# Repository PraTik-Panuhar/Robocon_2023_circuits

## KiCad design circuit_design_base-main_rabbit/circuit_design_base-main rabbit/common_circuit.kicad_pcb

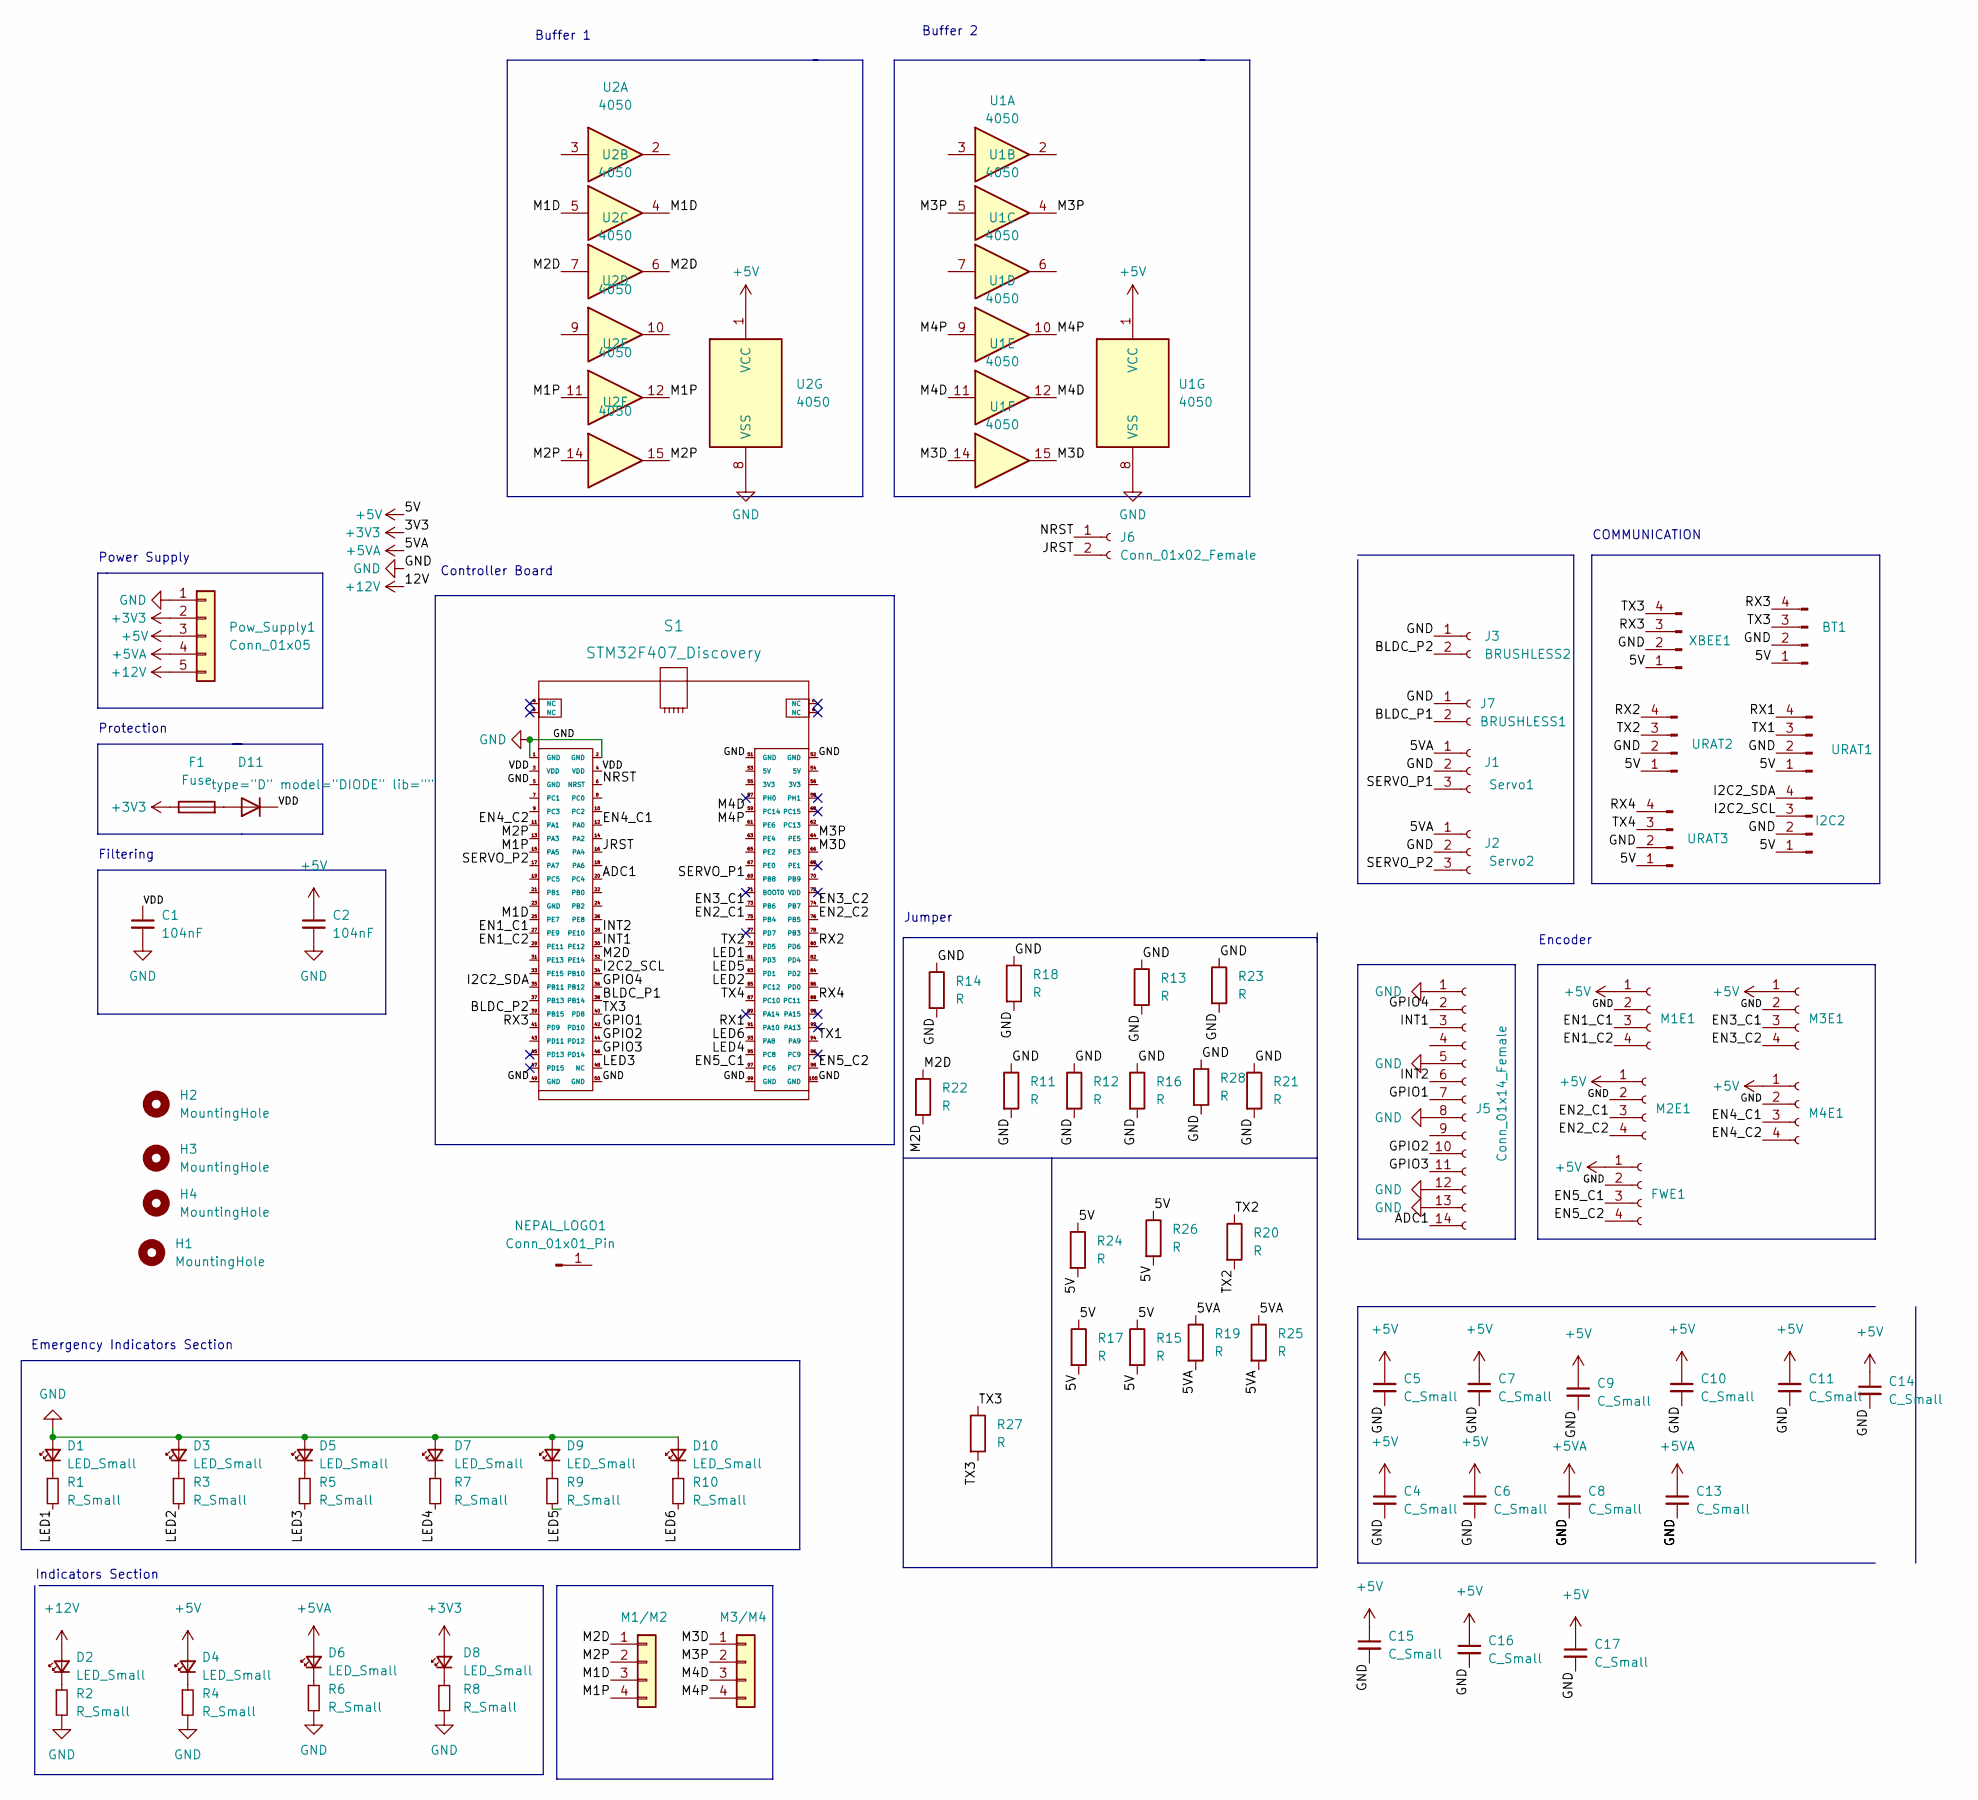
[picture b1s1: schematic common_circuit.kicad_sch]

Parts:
BT1: Conn_01x04_Male; jst_4
C1, C2: 104nF; Capacitor_Disc_Small
C4, C5, C6, C7, C8, C9, C10, C11, C13, C14, C15, C16, C17: C_Small; Capacitor_Disc_Small
D1, D2, D3, D4, D5, D6, D7, D8, D9, D10: LED_Small; LED_D3.0mm
D11: type="D" model="DIODE" lib=""; Diode_Medium
F1: Fuse; Fuse_Holder
FWE1: Conn_01x04_Female; jst_4
H1, H2, H3, H4: MountingHole; MountingHole_3mm_Pad
I2C2: I2C1; jst_4
J1: Servo1; JST_EH_B3B-EH-A_1x03_P2.50mm_Vertical
J2: Servo2; JST_EH_B3B-EH-A_1x03_P2.50mm_Vertical
J3: BRUSHLESS2; PinHeader_1x02_P2.54mm_Vertical
J5: Conn_01x14_Female; IDC-Header_2x07_P2.54mm_Latch_Vertical
J6: Conn_01x02_Female; PinHeader_1x02_P2.54mm_Vertical
J7: BRUSHLESS1; PinHeader_1x02_P2.54mm_Vertical
M1/M2, M3/M4: Conn_01x04; jst_4
M1E1, M2E1, M3E1, M4E1: Conn_01x04_Female; jst_4
NEPAL_LOGO1: Conn_01x01_Pin; nepalLogo
Pow_Supply1: Conn_01x05; JST_5_BIG
R1, R2, R3, R4, R5, R6, R7, R8, R9, R10: R_Small; Resistor_small
R11, R12, R13, R14, R15, R16, R17, R18, R19, R21, R22, R23, R25, R26, R28: R; Resistor_small
R20, R24, R27: R; R_Axial_DIN0207_L6.3mm_D2.5mm_P15.24mm_Horizontal
S1: STM32F407_Discovery
U1, U2: 4050; DIP-16_W7.62mm_LongPads
URAT1, URAT2, URAT3: Conn_01x04_Male; jst_4
XBEE1: Conn_01x04_Male; jst_4

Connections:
+3V3: D8.2 (A), F1.1, Pow_Supply1.2
+5V: BT1.1, C2.1, C4.1, C5.1, C6.1, C7.1, C9.1, C10.1, C11.1, C14.1, C15.1, C16.1, C17.1, D4.2 (A), FWE1.1, I2C2.1, M1E1.1, M2E1.1, M3E1.1, M4E1.1, Pow_Supply1.3, R15.1, R15.2, R17.1, R17.2, R24.1, R24.2, R26.1, R26.2, U1.1 (VCC), U2.1 (VCC), URAT1.1, URAT2.1, URAT3.1, XBEE1.1
+5VA: C8.1, C13.1, D6.2 (A), J1.1, J2.1, Pow_Supply1.4, R19.1, R19.2, R25.1, R25.2
+12V: D2.2 (A), Pow_Supply1.5
/ADC1: J5.14, S1.20 (PC4)
/BLDC_P1: J7.2, S1.38 (PB14)
/BLDC_P2: J3.2, S1.39 (PB15)
/EN1_C1: M1E1.3, S1.27 (PE9)
/EN1_C2: M1E1.4, S1.29 (PE11)
/EN2_C1: M2E1.3, S1.75 (PB4)
/EN2_C2: M2E1.4, S1.76 (PB5)
/EN3_C1: M3E1.3, S1.73 (PB6)
/EN3_C2: M3E1.4, S1.74 (PB7)
/EN4_C1: M4E1.3, S1.12 (PA0)
/EN4_C2: M4E1.4, S1.11 (PA1)
/EN5_C1: FWE1.3, S1.97 (PC6)
/EN5_C2: FWE1.4, S1.98 (PC7)
/GPIO1: J5.7, S1.42 (PD10)
/GPIO2: J5.10, S1.44 (PD12)
/GPIO3: J5.11, S1.46 (PD14)
/GPIO4: J5.2, S1.36 (PB12)
/I2C2_SCL: I2C2.3, S1.34 (PB10)
/I2C2_SDA: I2C2.4, S1.35 (PB11)
/INT1: J5.3, S1.30 (PE12)
/INT2: J5.6, S1.28 (PE10)
/JRST: J6.2, S1.16 (PA4)
/LED1: R1.2, S1.81 (PD3)
/LED2: R3.2, S1.85 (PC12)
/LED3: R5.2, S1.48 (NC)
/LED4: R7.2, S1.95 (PC8)
/LED5: R9.2, S1.83 (PD1)
/LED6: R10.2, S1.93 (PA8)
/M1D: M1/M2.3, S1.25 (PE7), U2.4, U2.5
/M1P: M1/M2.4, S1.15 (PA5), U2.11, U2.12
/M2D: M1/M2.1, R22.1, R22.2, S1.32 (PE14), U2.6, U2.7
/M2P: M1/M2.2, S1.13 (PA3), U2.14, U2.15
/M3D: M3/M4.1, S1.66 (PE3), U1.14, U1.15
/M3P: M3/M4.2, S1.64 (PE5), U1.4, U1.5
/M4D: M3/M4.3, S1.59 (PC14), U1.11, U1.12
/M4P: M3/M4.4, S1.61 (PE6), U1.9, U1.10
/NRST: J6.1, S1.6 (NRST)
/RX1: S1.91 (PA10), URAT1.4
/RX2: S1.80 (PD6), URAT2.4
/RX3: BT1.4, S1.41 (PD9), XBEE1.3
/RX4: S1.88 (PC11), URAT3.4
/SERVO_P1: J1.3, S1.69 (PB8)
/SERVO_P2: J2.3, S1.17 (PA7)
/TX1: S1.94 (PA9), URAT1.3
/TX2: R20.1, R20.2, S1.79 (PD5), URAT2.3
/TX3: BT1.3, R27.1, R27.2, S1.40 (PD8), XBEE1.4
/TX4: S1.87 (PC10), URAT3.3
/VDD: C1.1, D11.2 (K), S1.3 (VDD), S1.4 (VDD)
GND: BT1.2, C1.2, C2.2, C4.2, C5.2, C6.2, C7.2, C8.2, C9.2, C10.2, C11.2, C13.2, C14.2, C15.2, C16.2, C17.2, D1.2 (A), D3.2 (A), D5.2 (A), D7.2 (A), D9.2 (A), D10.2 (A), FWE1.2, I2C2.2, J1.2, J2.2, J3.1, J5.1, J5.5, J5.8, J5.12, J5.13, J7.1, M1E1.2, M2E1.2, M3E1.2, M4E1.2, Pow_Supply1.1, R2.2, R4.2, R6.2, R8.2, R11.1, R11.2, R12.1, R12.2, R13.1, R13.2, R14.1, R14.2, R16.1, R16.2, R18.1, R18.2, R21.1, R21.2, R23.1, R23.2, R28.1, R28.2, S1.1 (GND), S1.2 (GND), S1.5 (GND), S1.49 (GND), S1.50 (GND), S1.51 (GND), S1.52 (GND), S1.99 (GND), S1.100 (GND), U1.8 (VSS), U2.8 (VSS), URAT1.2, URAT2.2, URAT3.2, XBEE1.2
unnamed: D1.1 (K), R1.1
unnamed: D2.1 (K), R2.1
unnamed: D3.1 (K), R3.1
unnamed: D4.1 (K), R4.1
unnamed: D5.1 (K), R5.1
unnamed: D6.1 (K), R6.1
unnamed: D7.1 (K), R7.1
unnamed: D8.1 (K), R8.1
unnamed: D9.1 (K), R9.1
unnamed: D10.1 (K), R10.1
unnamed: D11.1 (A), F1.2

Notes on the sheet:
Encoder
Indicators Section
Buffer 1
Emergency Indicators Section
COMMUNICATION
Jumper
Filtering
Power Supply
Protection
Controller Board
Buffer 2

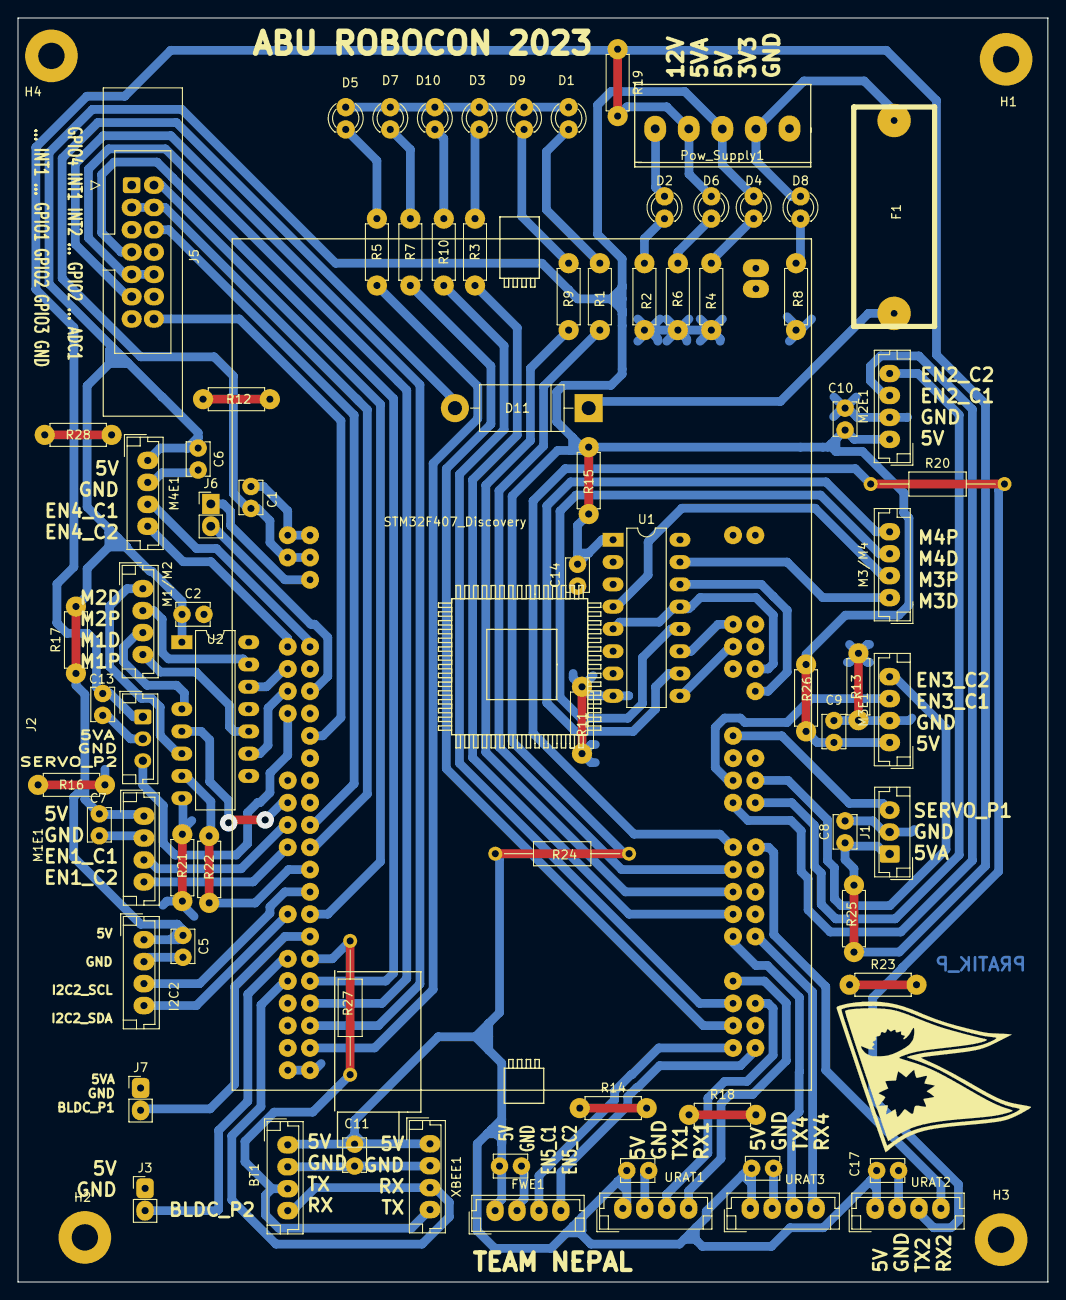
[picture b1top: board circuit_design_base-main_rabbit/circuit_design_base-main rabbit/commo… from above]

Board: 2 copper layers, 117.3 x 144.0 mm, 83 parts (0 on the bottom side), 64 nets.

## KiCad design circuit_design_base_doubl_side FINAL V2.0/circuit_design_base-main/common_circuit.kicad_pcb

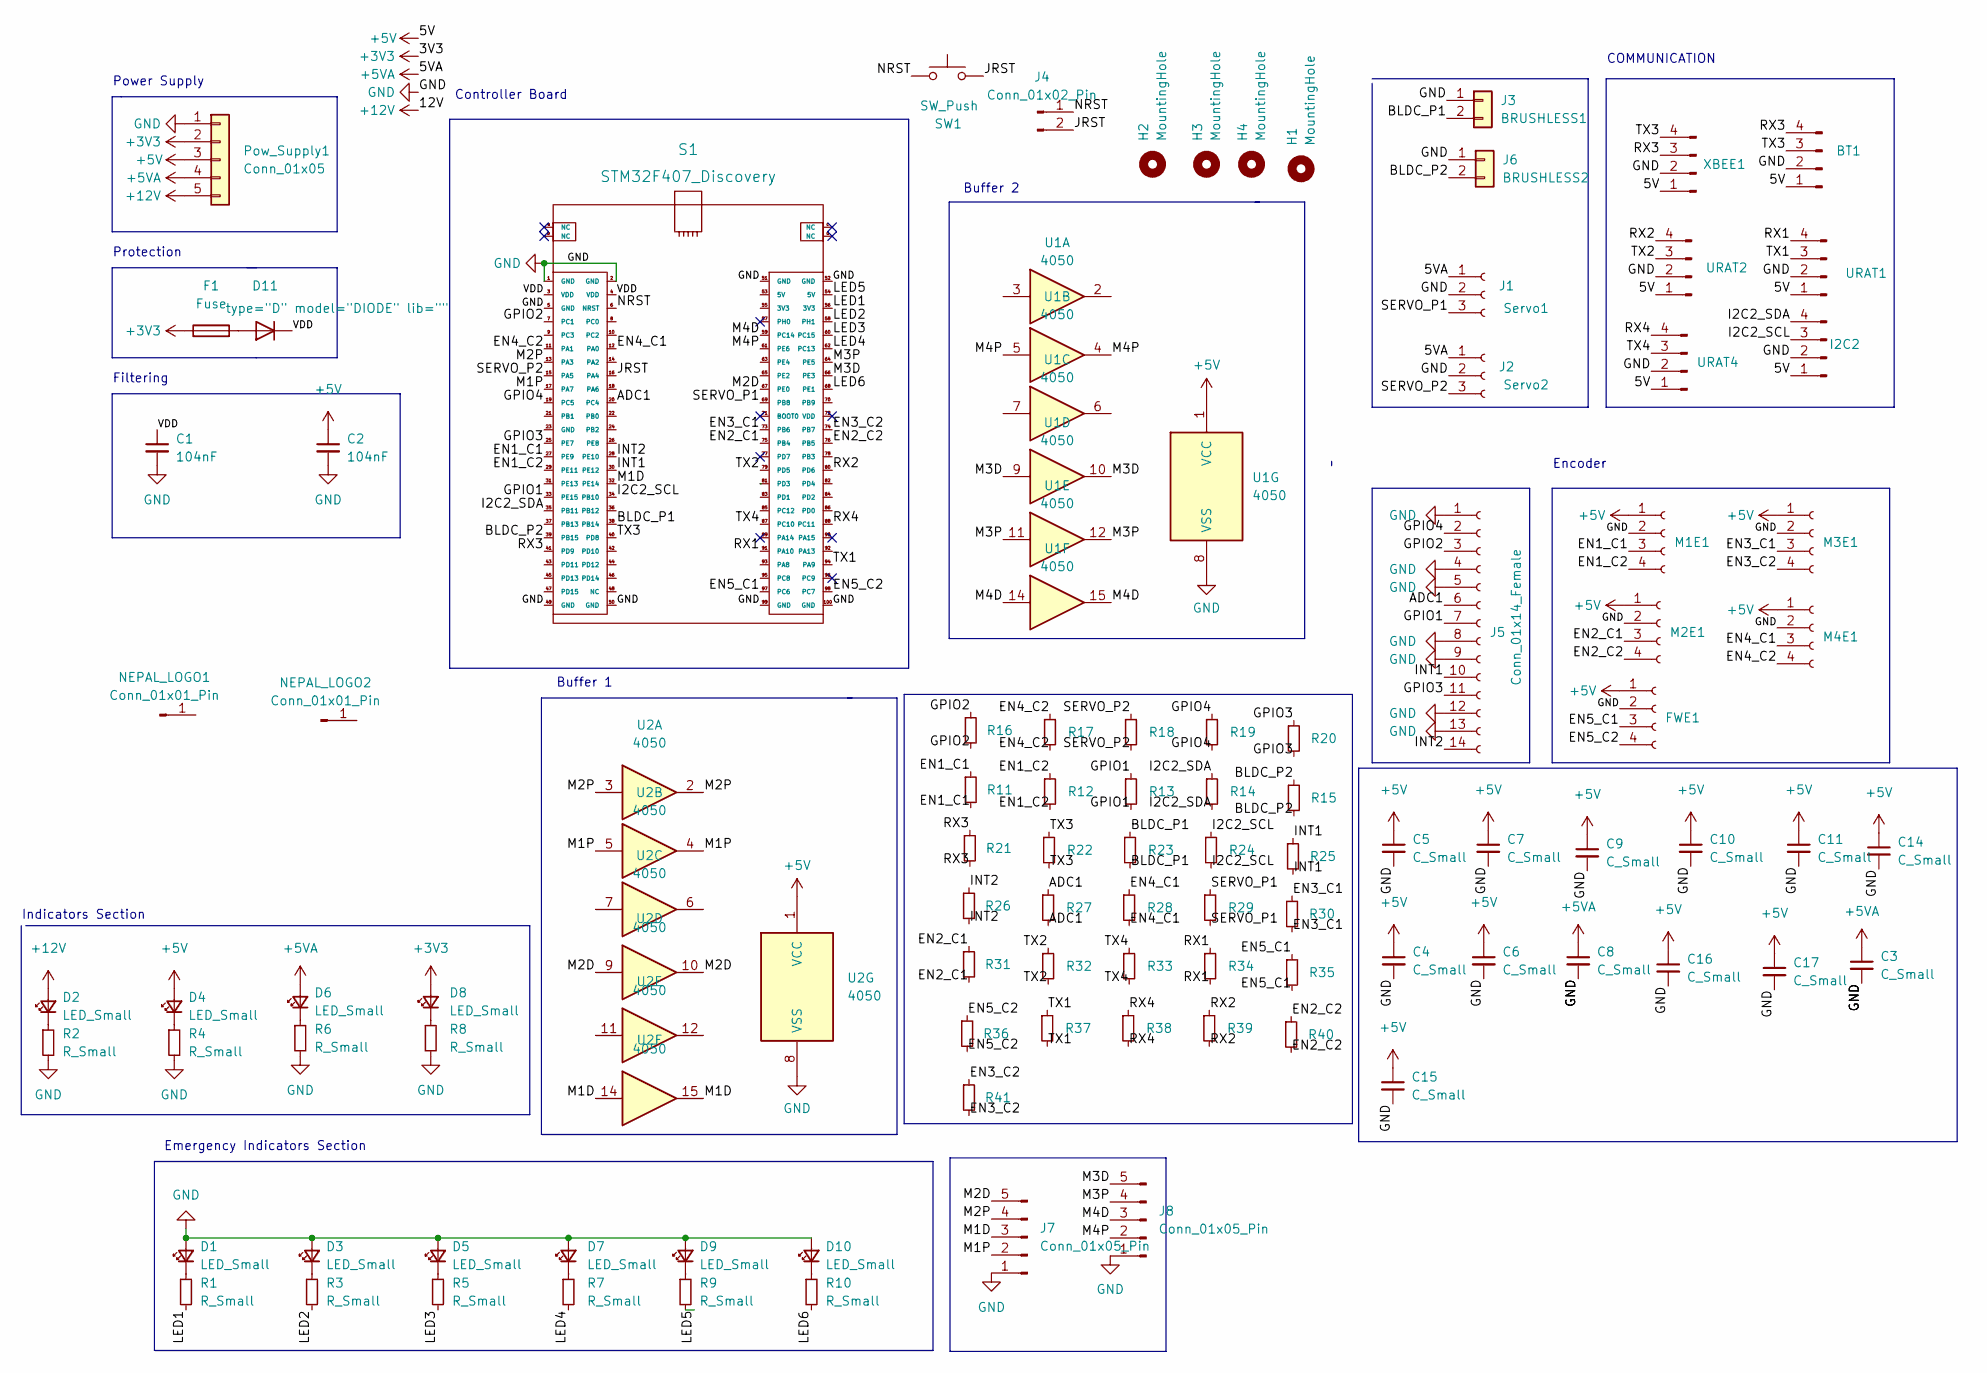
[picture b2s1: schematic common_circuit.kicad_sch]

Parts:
BT1: Conn_01x04_Male; jst_4
C1, C2: 104nF; C_0603_1608Metric_Pad1.08x0.95mm_HandSolder
C3, C4, C5, C6, C7, C8, C9, C10, C11, C14, C15, C16, C17: C_Small; C_0603_1608Metric_Pad1.08x0.95mm_HandSolder
D1, D2, D3, D4, D5, D6, D7, D8, D9, D10: LED_Small; LED_1206_3216Metric_Pad1.42x1.75mm_HandSolder
D11: type="D" model="DIODE" lib=""; Diode_Small
F1: Fuse; Fuse_Holder
FWE1: Conn_01x04_Female; jst_4
H1, H2, H3, H4: MountingHole; MountingHole_3mm_Pad
I2C2: I2C1; jst_4
J1: Servo1; JST_EH_B3B-EH-A_1x03_P2.50mm_Vertical
J2: Servo2; JST_EH_B3B-EH-A_1x03_P2.50mm_Vertical
J3: BRUSHLESS1; PinSocket_1x02_P2.54mm_Vertical
J4: Conn_01x02_Pin; JST_EH_B2B-EH-A_1x02_P2.50mm_Vertical
J5: Conn_01x14_Female; IDC-Header_2x07_P2.54mm_Vertical
J6: BRUSHLESS2; PinSocket_1x02_P2.54mm_Vertical
J7, J8: Conn_01x05_Pin; JST_EH_B5B-EH-A_1x05_P2.50mm_Vertical
M1E1, M2E1, M3E1, M4E1: Conn_01x04_Female; jst_4
NEPAL_LOGO1, NEPAL_LOGO2: Conn_01x01_Pin; nepalLogo
Pow_Supply1: Conn_01x05; JST_5_BIG
R1, R2, R3, R4, R5, R6, R7, R8, R9, R10, R11, R12, R13, R14, R15, R16, R17, R18, R19, R20, R21, R22, R23, R24, R25, R26, R27, R28, R29, R30, R31, R32, R33, R34, R35, R36, R37, R38, R39, R40, R41: R_Small; R_0603_1608Metric_Pad0.98x0.95mm_HandSolder
S1: STM32F407_Discovery
SW1: SW_Push; SW_PUSH_6mm
U1, U2: 4050; DIP-16_W7.62mm_LongPads
URAT1, URAT2, URAT4: Conn_01x04_Male; jst_4
XBEE1: Conn_01x04_Male; jst_4

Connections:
+3V3: D8.2 (A), F1.1, Pow_Supply1.2
+5V: BT1.1, C2.1, C4.1, C5.1, C6.1, C7.1, C9.1, C10.1, C11.1, C14.1, C15.1, C16.1, C17.1, D4.2 (A), FWE1.1, I2C2.1, M1E1.1, M2E1.1, M3E1.1, M4E1.1, Pow_Supply1.3, U1.1 (VCC), U2.1 (VCC), URAT1.1, URAT2.1, URAT4.1, XBEE1.1
+5VA: C3.1, C8.1, D6.2 (A), J1.1, J2.1, Pow_Supply1.4
+12V: D2.2 (A), Pow_Supply1.5
/ADC1: J5.6, R27.1, R27.2, S1.20 (PC4)
/BLDC_P1: J3.2, R23.1, R23.2, S1.38 (PB14)
/BLDC_P2: J6.2, R15.1, R15.2, S1.39 (PB15)
/EN1_C1: M1E1.3, R11.1, R11.2, S1.27 (PE9)
/EN1_C2: M1E1.4, R12.1, R12.2, S1.29 (PE11)
/EN2_C1: M2E1.3, R31.1, R31.2, S1.75 (PB4)
/EN2_C2: M2E1.4, R40.1, R40.2, S1.76 (PB5)
/EN3_C1: M3E1.3, R30.1, R30.2, S1.73 (PB6)
/EN3_C2: M3E1.4, R41.1, R41.2, S1.74 (PB7)
/EN4_C1: M4E1.3, R28.1, R28.2, S1.12 (PA0)
/EN4_C2: M4E1.4, R17.1, R17.2, S1.11 (PA1)
/EN5_C1: FWE1.3, R35.1, R35.2, S1.97 (PC6)
/EN5_C2: FWE1.4, R36.1, R36.2, S1.98 (PC7)
/GPIO1: J5.7, R13.1, R13.2, S1.33 (PE15)
/GPIO2: J5.3, R16.1, R16.2, S1.7 (PC1)
/GPIO3: J5.11, R20.1, R20.2, S1.25 (PE7)
/GPIO4: J5.2, R19.1, R19.2, S1.19 (PC5)
/I2C2_SCL: I2C2.3, R24.1, R24.2, S1.34 (PB10)
/I2C2_SDA: I2C2.4, R14.1, R14.2, S1.35 (PB11)
/INT1: J5.10, R25.1, R25.2, S1.30 (PE12)
/INT2: J5.14, R26.1, R26.2, S1.28 (PE10)
/JRST: J4.2, S1.16 (PA4), SW1.2
/LED1: R1.2, S1.56 (3V3)
/LED2: R3.2, S1.58 (PH1)
/LED3: R5.2, S1.60 (PC15)
/LED4: R7.2, S1.62 (PC13)
/LED5: R9.2, S1.54 (5V)
/LED6: R10.2, S1.68 (PE1)
/M1D: J7.3, S1.32 (PE14), U2.14, U2.15
/M1P: J7.2, S1.17 (PA7), U2.4, U2.5
/M2D: J7.5, S1.67 (PE0), U2.9, U2.10
/M2P: J7.4, S1.13 (PA3), U2.2, U2.3
/M3D: J8.5, S1.66 (PE3), U1.9, U1.10
/M3P: J8.4, S1.64 (PE5), U1.11, U1.12
/M4D: J8.3, S1.59 (PC14), U1.14, U1.15
/M4P: J8.2, S1.61 (PE6), U1.4, U1.5
/NRST: J4.1, S1.6 (NRST), SW1.1
/RX1: R34.1, R34.2, S1.91 (PA10), URAT1.4
/RX2: R39.1, R39.2, S1.80 (PD6), URAT2.4
/RX3: BT1.4, R21.1, R21.2, S1.41 (PD9), XBEE1.3
/RX4: R38.1, R38.2, S1.88 (PC11), URAT4.4
/SERVO_P1: J1.3, R29.1, R29.2, S1.69 (PB8)
/SERVO_P2: J2.3, R18.1, R18.2, S1.15 (PA5)
/TX1: R37.1, R37.2, S1.94 (PA9), URAT1.3
/TX2: R32.1, R32.2, S1.79 (PD5), URAT2.3
/TX3: BT1.3, R22.1, R22.2, S1.40 (PD8), XBEE1.4
/TX4: R33.1, R33.2, S1.87 (PC10), URAT4.3
/VDD: C1.1, D11.2 (K), S1.3 (VDD), S1.4 (VDD)
GND: BT1.2, C1.2, C2.2, C3.2, C4.2, C5.2, C6.2, C7.2, C8.2, C9.2, C10.2, C11.2, C14.2, C15.2, C16.2, C17.2, D1.2 (A), D3.2 (A), D5.2 (A), D7.2 (A), D9.2 (A), D10.2 (A), FWE1.2, I2C2.2, J1.2, J2.2, J3.1, J5.1, J5.4, J5.5, J5.8, J5.9, J5.12, J5.13, J6.1, J7.1, J8.1, M1E1.2, M2E1.2, M3E1.2, M4E1.2, Pow_Supply1.1, R2.2, R4.2, R6.2, R8.2, S1.1 (GND), S1.2 (GND), S1.5 (GND), S1.49 (GND), S1.50 (GND), S1.51 (GND), S1.52 (GND), S1.99 (GND), S1.100 (GND), U1.8 (VSS), U2.8 (VSS), URAT1.2, URAT2.2, URAT4.2, XBEE1.2
unnamed: D1.1 (K), R1.1
unnamed: D2.1 (K), R2.1
unnamed: D3.1 (K), R3.1
unnamed: D4.1 (K), R4.1
unnamed: D5.1 (K), R5.1
unnamed: D6.1 (K), R6.1
unnamed: D7.1 (K), R7.1
unnamed: D8.1 (K), R8.1
unnamed: D9.1 (K), R9.1
unnamed: D10.1 (K), R10.1
unnamed: D11.1 (A), F1.2

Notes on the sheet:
Encoder
Indicators Section
Buffer 1
Emergency Indicators Section
COMMUNICATION
Filtering
Power Supply
Protection
Controller Board
Buffer 2

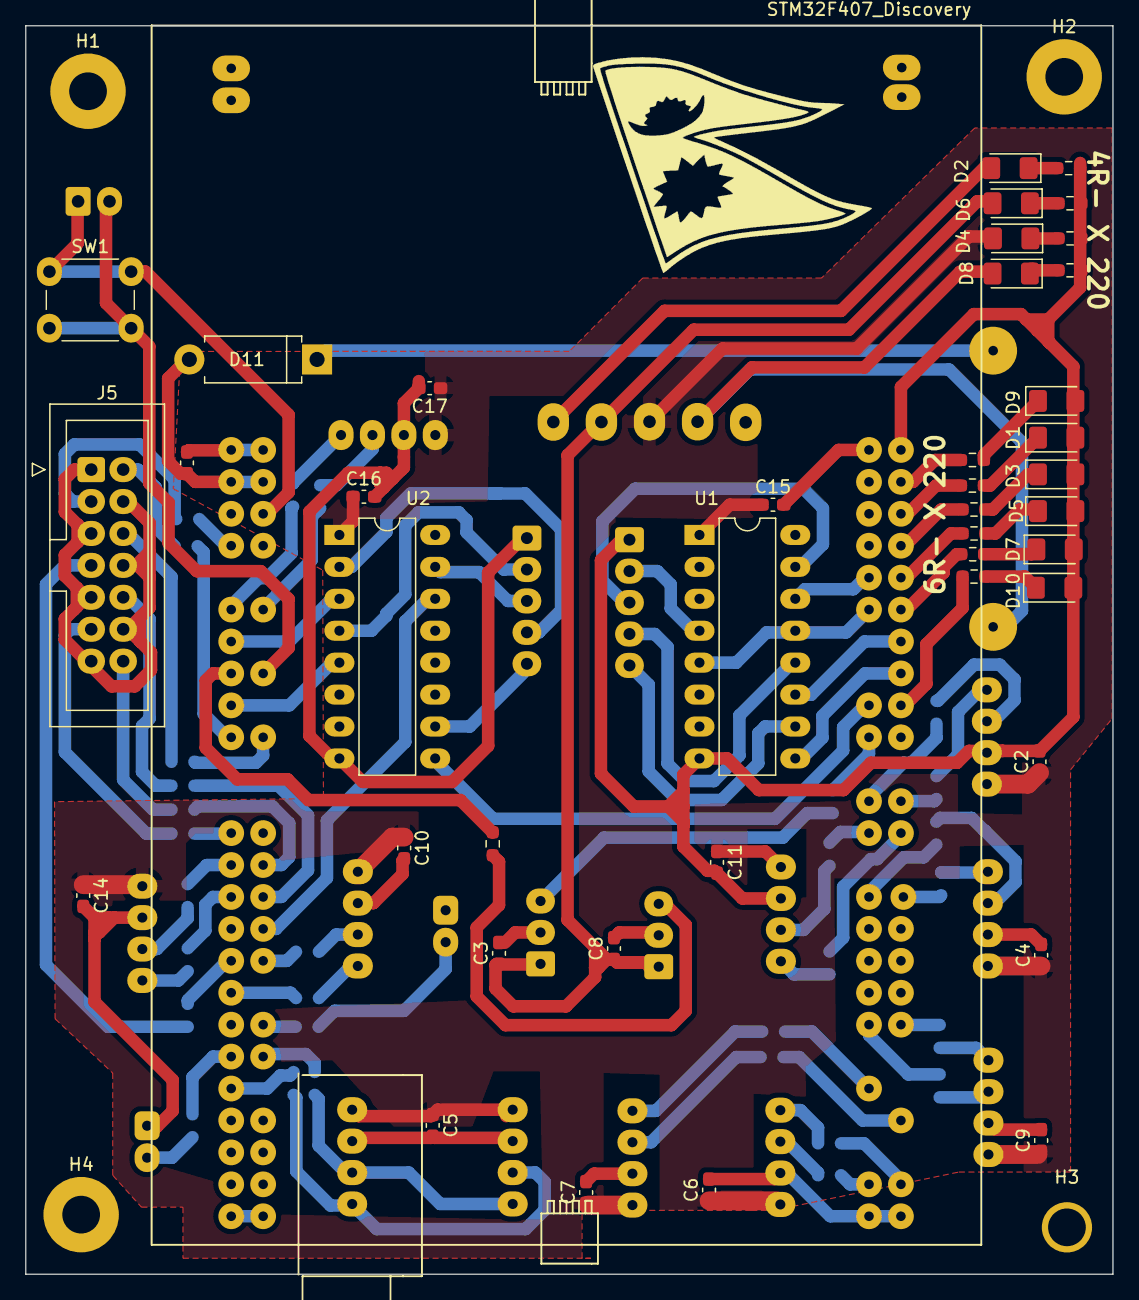
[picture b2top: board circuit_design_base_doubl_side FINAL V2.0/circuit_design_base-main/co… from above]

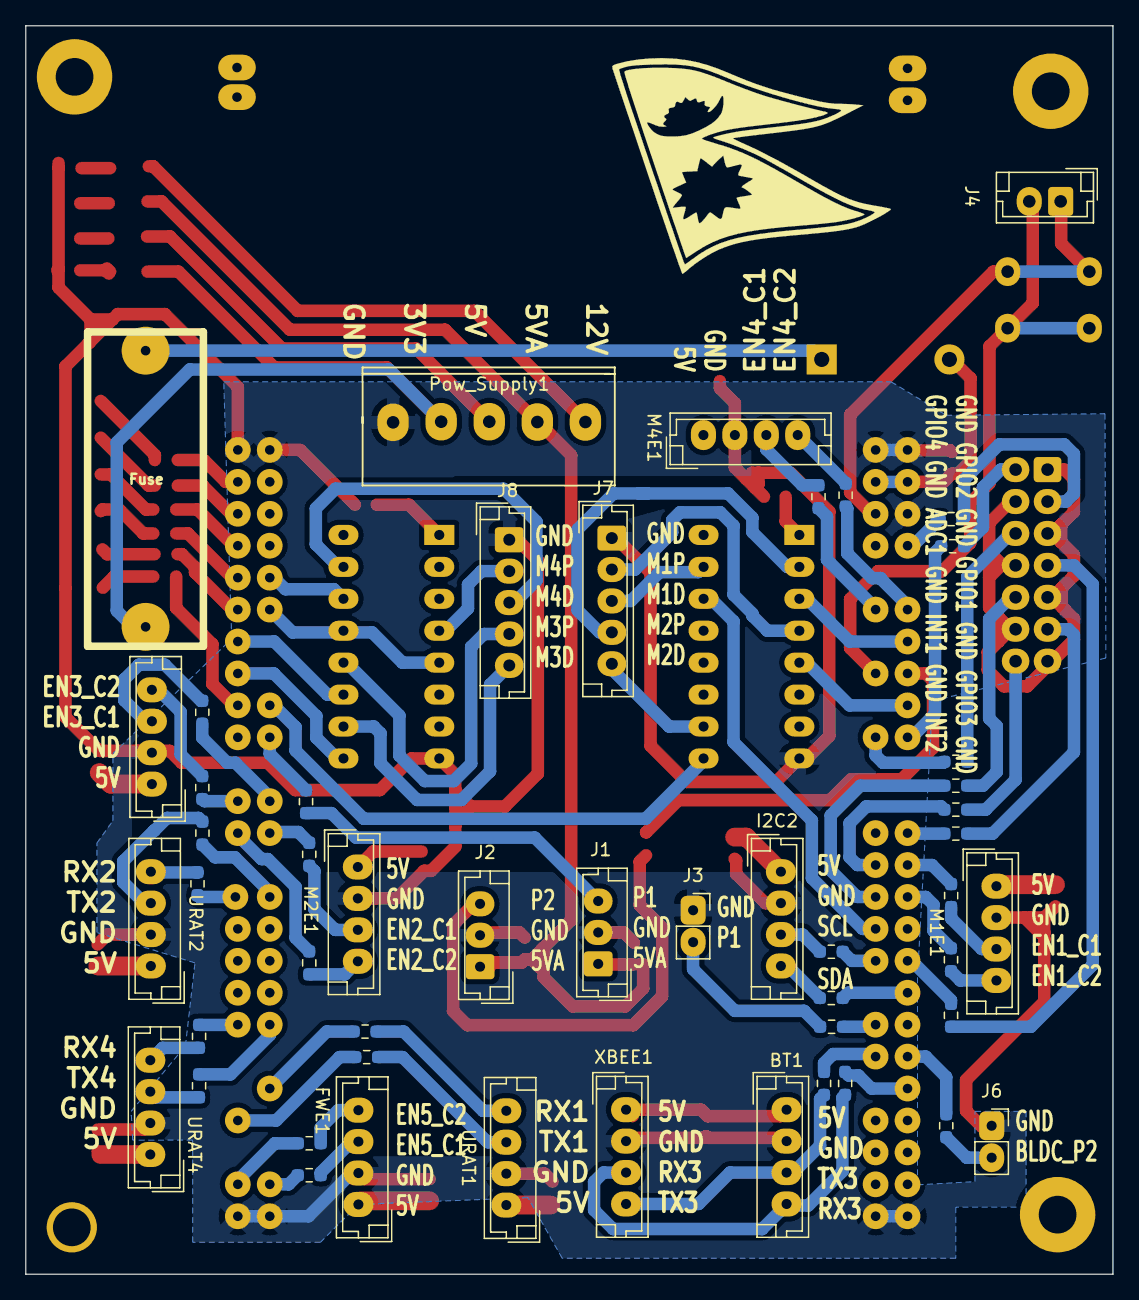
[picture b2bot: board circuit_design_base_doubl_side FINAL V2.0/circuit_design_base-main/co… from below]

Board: 2 copper layers, 86.5 x 99.3 mm, 98 parts (51 on the bottom side), 64 nets.

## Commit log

2024-02-13 Robocon 2023 circuit
